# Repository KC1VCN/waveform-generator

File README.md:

# Simple Waveform Generator

## Introduction

The waveform generator is a simple printed circuit board (PCB) designed to generate sinusoidal, triangular, and square waveforms, with usable frequencies up to 10 MHz depending on the waveform type and acceptable output distortion or attenuation. The PCB was designed as an Arduino UNO R3 shield, with the Arduino board acting as the controller. Commands can be sent through the USB port from a computer using a simple Python GUI or hardware API, providing both graphical and programmatic control.

The board also has four external digital inputs with debouncing circuits. These inputs can be connected to rotary encoders to adjust the signal frequency and amplitude. This feature is useful for implementing a standalone audio signal generator in a small enclosure.

The waveform generator PCB supports adjustment of the following output signal parameters:

- Frequency
- Amplitude
- DC offset
- Waveform type (sinusoid, triangle, or square)

The following files are provided as part of this project:

- KiCad v10.0.0 project files for the complete PCB
- Firmware source code for the Arduino UNO R3 and the associated `Makefile`
- Python GUI and hardware API

The following sections provide more details about the circuit design, PCB implementation, software control, and measurement results. The supplied files are intended to help users reproduce the hardware and explore its capabilities.

---

## Printed Circuit Board

Photographs of the waveform generator PCB is shown in Figs. 1a–b. The bare PCB was manufactured through DigiKey's DKRed program using a four-layer stackup (www.digikey.com).

<figure>
  
  <figcaption><b>Figure 1a:</b> Printed circuit board of the waveform generator.</figcaption>
</figure>
<br>
<br>

<figure>
  
  <figcaption><b>Figure 1b:</b> Waveform generator attached to Arduino UNO R3.</figcaption>
</figure>
<br>
<br>

The stackup of the PCB is shown in Fig. 2.

<figure>
  
  <figcaption><b>Figure 2:</b> PCB stackup (DigiKey DKRed four-layer stackup).</figcaption>
</figure>
<br>
<br>

All surface-mount components were selected in 0603 or larger package sizes, and all IC packages were chosen without a central exposed pad and with a lead pitch of at least 0.5 mm. These choices make manual PCB assembly easier if necessary. 

For manual assembly, it is recommended to solder the header pins first while the PCB, header pins, and Arduino board are stacked together. This helps ensure that the header pins align properly with the Arduino board. Then, perform a basic DC test by powering the Arduino board and verifying the +5 V and +3.3 V supply rails on the PCB. You may then proceed with the remaining components. An ESD-dissipative work surface and wrist strap are strongly recommended. A binocular microscope is also useful for manual assembly. Finally, liquid rosin solder flux can significantly help when soldering fine-pitch IC packages by allowing the solder to flow more smoothly.

---

## Connecting the Waveform Generator

To program the Arduino UNO R3 microcontroller or control the waveform generator, connect the Arduino board to your computer using a USB cable. No additional drivers should normally be required on Linux. However, you may need to add your user account to the `dialout` group to access the USB serial port. The waveform generator receives its power from the Arduino board.

Control commands for the waveform generator are sent through the same Arduino UNO R3 USB connector. Therefore, only one application (the GUI, hardware API, or programming tool) should access the serial port at a time.

> [!NOTE]
> When the computer software opens the serial port, the Arduino board may reset as part of the normal bootloader startup sequence. If programming is not initiated, the microcontroller proceeds to the application's `main` function. Allow sufficient time for this startup sequence after opening the serial port, since the microcontroller cannot process commands immediately.

---

## Waveform Generation

The core of the waveform generator PCB is the Analog Devices AD9833 programmable waveform generator IC. With a 25 MHz reference clock, this chip supports output frequencies up to 12.5 MHz and provides a 28-bit frequency tuning word. It has two frequency registers and two phase registers, enabling FSK and PSK modulation. Once these registers are programmed with the desired frequency or phase values, the output can be switched using a register-select command. Sinusoidal, triangular, and square waveforms are supported. Since the signal path following the AD9833 is DC-coupled (with no DC-blocking capacitor), the PCB can also generate signals at very low frequencies.

To suppress unwanted high-frequency spectral components, a fifth-order elliptic reconstruction (anti-imaging) low-pass filter was designed after the AD9833. This provides a relatively clean output spectrum at frequencies up to 10 MHz. Without this filter, spectral images from the sampled waveform would become increasingly close to the desired signal as the output frequency approaches the Nyquist frequency. A relatively sharp cutoff is therefore desirable, motivating the choice of an elliptic filter design.

### Gain Control

The gain control block is based on a multiplying digital-to-analog converter (DAC) architecture. For this purpose, the Analog Devices AD5452 12-bit high-bandwidth multiplying DAC and AD8062 operational amplifier were used. This configuration provides an output voltage swing of one polarity before DC-offset adjustment. Although this approach offers a wide gain adjustment range, the DAC and the associated high-frequency compensation of the op-amp limit the overall bandwidth of the waveform generator.

### DC Offset

Since the AD8062 op-amp in the gain control stage is used in an inverting configuration, its output is negative before offset adjustment. A DC-offset control was therefore implemented to shift the output DC level. This helps to generate output waveforms with symmetric swings. The Analog Devices AD5270 digital potentiometer provides an adjustable voltage to the noninverting input of the AD8062. A series capacitor can also be added at the output to block DC completely if necessary. Note, however, that this would introduce a low-frequency cutoff.

Two points are worth mentioning regarding the AD5270 compared with the AD9833 and AD5452. First, the SPI timing configuration used for the AD5270 is CPOL = 0 and CPHA = 1, whereas the AD9833 and AD5452 are driven using CPOL = 1 and CPHA = 0. This difference must be handled in software because the ICs share the SPI clock line from the Arduino UNO R3. Second, a pull-up resistor is required on the AD5270 SPI data output (SDO) pin, even if readback is not used. Analog Devices Product/Process Change Notice PCN 10_0354 (December 14, 2010) describes a potential malfunction if the pin is left floating.

### Negative Voltage Supply

To generate the negative supply voltage required by the AD8062 op-amp, the Analog Devices MAX1680 switched-capacitor voltage converter was used. Low-ESR ceramic capacitors are important for efficient charge-pump operation and for minimizing switching ripple on the generated supply rail.

---

## Rotary Encoder Inputs

The waveform generator board supports two rotary encoders for adjusting frequency and amplitude when configured as a standalone audio signal generator. One suitable example is the Bourns `PEC09-2315F-N0015` rotary encoder. The connection diagram for the encoders is shown in Fig. 3.

<figure>
  
  <figcaption><b>Figure 3:</b> Connection diagram of the rotary encoders for a standalone waveform generator.</figcaption>
</figure>
<br>
<br>

In standalone operation, the generator remains within the frequency and gain limits preset in the firmware. The default limits are listed below and can be modified in the firmware source code:

| Parameter           | Value       |
|---------------------|-------------|
| Minimum frequency   | 20 Hz       |
| Maximum frequency   | 20,000 Hz   |
| Frequency step      | 100 Hz      |
| Minimum gain        | 0           |
| Maximum gain        | 4095        |
| Gain step           | 100         |

---

## Measurement Results

This section presents basic measurement results for the waveform generator. All measurements were performed using a Siglent SVA-1015X spectrum analyzer at room temperature. Note that these measurements are intended to characterize the performance of the waveform generator under the test conditions used and should not be interpreted as guaranteed specifications over the full range of operating conditions.

Fig. 4 shows the sinusoidal output level versus frequency at different gain settings. For a given gain setting, the output level remains nearly constant up to 2 MHz. Above 2 MHz, the level begins to decrease due to the limited bandwidth of the signal chain.

<figure>
  
  <figcaption><b>Figure 4:</b> Output signal level vs. frequency.</figcaption>
</figure>
<br>
<br>

Fig. 5 shows the sinusoidal output level versus gain setting at different frequencies. The generator provides approximately 50 dB of linear gain-control range up to 100 kHz. Beginning near 1 MHz, this range decreases, reaching approximately 35 dB at 2 MHz.

<figure>
  
  <figcaption><b>Figure 5:</b> Output signal level vs. gain setting.</figcaption>
</figure>
<br>
<br>

The output spectra of sinusoidal signals at different frequencies are shown in Figs. 6a–e. The gain setting for these measurements was 2048 (half scale). 

<figure>
  
  <figcaption><b>Figure 6a:</b> Harmonic levels at 10 kHz (gain: 2048).</figcaption>
</figure>
<br>
<br>

<figure>
  
  <figcaption><b>Figure 6b:</b> Harmonic levels at 100 kHz (gain: 2048).</figcaption>
</figure>
<br>
<br>

<figure>
  
  <figcaption><b>Figure 6c:</b> Harmonic levels at 1 MHz (gain: 2048).</figcaption>
</figure>
<br>
<br>

<figure>
  
  <figcaption><b>Figure 6d:</b> Harmonic levels at 2 MHz (gain: 2048).</figcaption>
</figure>
<br>
<br>

<figure>
  
  <figcaption><b>Figure 6e:</b> Harmonic levels at 10 MHz (gain: 2048).</figcaption>
</figure>
<br>
<br>

---

## FSK and PSK Modulation

The controller also provides a simple way to test the frequency-shift keying (FSK) and phase-shift keying (PSK) capabilities of the AD9833. These features are intended only for demonstration and have not been optimized for performance. You can experiment with them using a spectrum analyzer with demodulation capabilities or a suitable demodulator. The transmitted test message is "Hello World!", but it can be changed in the Python GUI.

At the beginning of each packet, the controller transmits the following synchronization sequence. The receiver should synchronize to this bit pattern for optimal results:

```text
10101010101010100000011100010010
```

Two hardware parameters may need adjustment for reliable operation. The first is the AD9833 reference-clock frequency, which determines the generated carrier frequencies. The PCB uses a nominal 25 MHz oscillator, but the actual frequency may differ slightly. The actual clock frequency can be estimated using a spectrum analyzer or measured directly with a frequency counter. The deviation from the nominal 25 MHz can be specified through the `CLOCK_TRIM` global variable in kHz. The default correction of 8.5 kHz was determined experimentally by matching the generated carrier frequency to the spectrum analyzer reading. Since this adjustment also depends on the accuracy of the spectrum analyzer's frequency reference, it should not be considered an absolute calibration. 

The second parameter is the microcontroller clock frequency, which affects the symbol timing. The Arduino UNO R3 normally operates at 16 MHz. For simplicity, symbol timing is implemented using software-controlled delay loops rather than hardware timer interrupts. These delays are adjusted to obtain a nominal symbol rate of 3 ksps, accounting for the additional execution time introduced by the AD9833 register select commands. Although a hardware timer-based approach would provide more predictable timing, software-controlled delays were considered sufficient for this demonstration. If the received eye diagram drifts, you may need to adjust these delays.

The following figures show FSK and binary PSK (BPSK) test results obtained using the waveform generator PCB.

<figure>
  
  <figcaption><b>Figure 7:</b> FSK modulation test of the waveform generator.</figcaption>
</figure>
<br>
<br>

<figure>
  
  <figcaption><b>Figure 8:</b> BPSK modulation test of the waveform generator.</figcaption>
</figure>
<br>
<br>

---

## Arduino UNO R3 Programming

The Arduino UNO R3 microcontroller can be programmed using the `avr-gcc` C compiler and the `avrdude` programming utility. The versions used during development are listed below:

| Design Tool    | Version                                     |
|----------------|---------------------------------------------|
| avr-gcc        | v7.3.0, AVR-8-bit-GNU-Toolchain-3.7.0-1796  |
| avrdude        | v7.3-20240715                               |

After installing these tools, download the firmware source files from the repository into a suitable directory. Then connect the Arduino UNO R3 board to your computer using a USB cable as described earlier.

> [!NOTE]
> After connecting the UNO R3 board, verify the serial device name assigned by Linux and update the `AVRDUDE_PORT` parameter in the `Makefile` accordingly.
>

> [!NOTE]
> Ensure that the directories containing the `avr-gcc` and `avrdude` executables are included in your `PATH` environment variable so Linux can locate the tools.
>

To compile the firmware, run the following command in the source directory:

```bash
make
```

To program the Arduino UNO R3 microcontroller, run:

```bash
make program
```

To remove previously compiled object files and start with a clean build, run:

```bash
make clean
```

---

## Graphical User Interface

A basic GUI and hardware API are provided to demonstrate the waveform generator's capabilities. Connecting an oscilloscope to the generator output while experimenting with the controls is recommended.

The GUI and hardware API were developed using **Python 3.9** on **Linux**. The reference platform was **RHEL 9.7**, although the software should also run on other Linux distributions if all dependencies are installed. The Python modules and versions used for the GUI and API are listed below. Note that the API itself requires only the `pyserial` module.

| Module      | Version |
|-------------|---------|
| PySide6     | 6.10.1  |
| pyserial    | 3.5     |

<figure>
  
  <figcaption><b>Figure 9:</b> GUI of the waveform generator.</figcaption>
</figure>
<br>
<br>

In the GUI, each register control provides a dial knob and a keyboard entry field. The up/down arrow keys and Page Up/Page Down keys adjust the dial values in normal and larger steps, respectively. The small selector buttons below the frequency display change the tuning multiplier for the frequency dial.

The entry fields allow register values to be entered directly from the keyboard. Signed values are also supported for quickly increasing or decreasing the corresponding register value. For example, entering `+1000` in the frequency field increases the displayed frequency by 1 kHz. Holding down the `Enter` key while the field is active repeatedly increases the frequency in 1 kHz steps. 

---

## Waveform Generator Command Reference

The waveform generator firmware provides a simple, SCPI-inspired command interface for controlling the waveform generator.

### Serial Port Settings

The default serial port settings used by the firmware are shown in the following Python snippet:

```python
port = serial.Serial(p.device)

port.baudrate=57600
port.bytesize=8
port.parity=serial.PARITY_NONE
port.stopbits=serial.STOPBITS_ONE
port.timeout=0.5

port.flushInput()
port.flushOutput()
```

### API Handshake

A simple handshake protocol is implemented between the firmware and the hardware API. Before sending a command to the Arduino, the API must wait until the microcontroller sends the `READY` word. The command can then be sent. After processing the command, the microcontroller returns the `DONE` word.

The following Python snippet can be used to read handshake messages from the microcontroller. Note that this function simply returns the received message without interpreting its contents. If no message is received within approximately one second, it returns False. The calling function must check the returned value (READY, DONE, or False) and respond accordingly.

```python
def wait():
    start_time = time.time()
    timeout_expiry = start_time + 1.0

    while time.time() < timeout_expiry:
        value = port.readline().decode().strip('\n')

        if (value != ''):
            return value
    
    return False
```

### Sending API Commands and Receiving Replies

The API supports two types of commands: those that set a parameter and those that query a parameter. A command can be sent to the microcontroller using the following Python snippet:

```python
port.write(command.encode())
```

For a command that queries a parameter, the microcontroller replies with a value. The returned value can be read using the following Python snippet:

```python
value = port.readline().decode().strip('\n')
```

Note that query commands return values stored in the microcontroller memory. In the current implementation, the microcontroller does not read back the actual chip registers over SPI. These queries therefore help verify that the microcontroller received the intended values from the computer, rather than confirming the chip register contents.

The available hardware API commands are described in the following sections.

### Set Output

```
output:<freq_select>:<phase_select>:\n
```

Selects the active frequency and phase output registers. Each register selection can be either `0` or `1`. 

The synthesizer provides two frequency registers and two phase registers. Once programmed, the active registers can be switched to provide FSK or PSK modulation.

### Set Waveform

```
wave:<type>:\n
```

Selects the output waveform type. The available values are `0` (sinusoid), `1` (triangle), `2` (square, *f*<sub>out</sub>/2), `3` (square, *f*<sub>out</sub>), and `4` (reset).

### Set Frequency

```
freq:<reg>:\n
```

Sets the frequency register value of the active output. The \<reg\> parameter must be between 0 and 268,435,455.

### Set Frequency in Hertz

```
freq-hz:<freq>:\n
```

Sets the frequency of the active output in hertz. The \<freq\> parameter must be between 0 and 10,000,000.

### Get Frequency

```
freq?:\n
```

Returns the frequency register value of the active output from the microcontroller.

### Set Phase

```
phase:<reg>:\n
```

Sets the phase register value of the active output. The \<reg\> parameter must be between 0 and 4095.

### Set Phase in Degrees

```
phase-deg:<phase>:\n
```

Sets the phase of the active output in degrees. The \<phase\> parameter must be between 0 and 360.

### Get Phase

```
phase?:\n
```

Returns the phase register value of the active output from the microcontroller.

### Set Gain

```
gain:<gain>:\n
```

Sets the gain register value. The \<gain\> parameter must be between 0 and 4095.

### Get Gain

```
gain?:\n
```

Returns the gain register value from the microcontroller.

### Set Offset

```
offset:<offset>:\n
```

Sets the DC offset register value. The \<offset\> parameter must be between 0 and 1023.

### Get Offset

```
offset?:\n
```

Returns the DC offset register value from the microcontroller.

---

## License

The hardware design, PCB design files, microcontroller firmware, Python software, and other source material in this repository are licensed under the **CERN Open Hardware Licence Version 2 – Weakly Reciprocal (CERN-OHL-W-2.0)**, unless otherwise noted.

Commercial use is permitted under the terms of CERN-OHL-W-2.0. Modified Covered Source must retain the applicable Notices and include the modification notice required by the license, including the date and a brief description of the modifications. Products made using the Covered Source must provide the Complete Source or identify the Source Location as required by the license.

The full license text is provided in the [`LICENSE`](LICENSE) file, and project-specific attribution and Source Location information are provided in the [`NOTICE`](NOTICE) file.

Third-party software used with this project, including avr-gcc, avrdude, and the required Python modules, is not part of the Covered Source in this repository and remains subject to its respective license.

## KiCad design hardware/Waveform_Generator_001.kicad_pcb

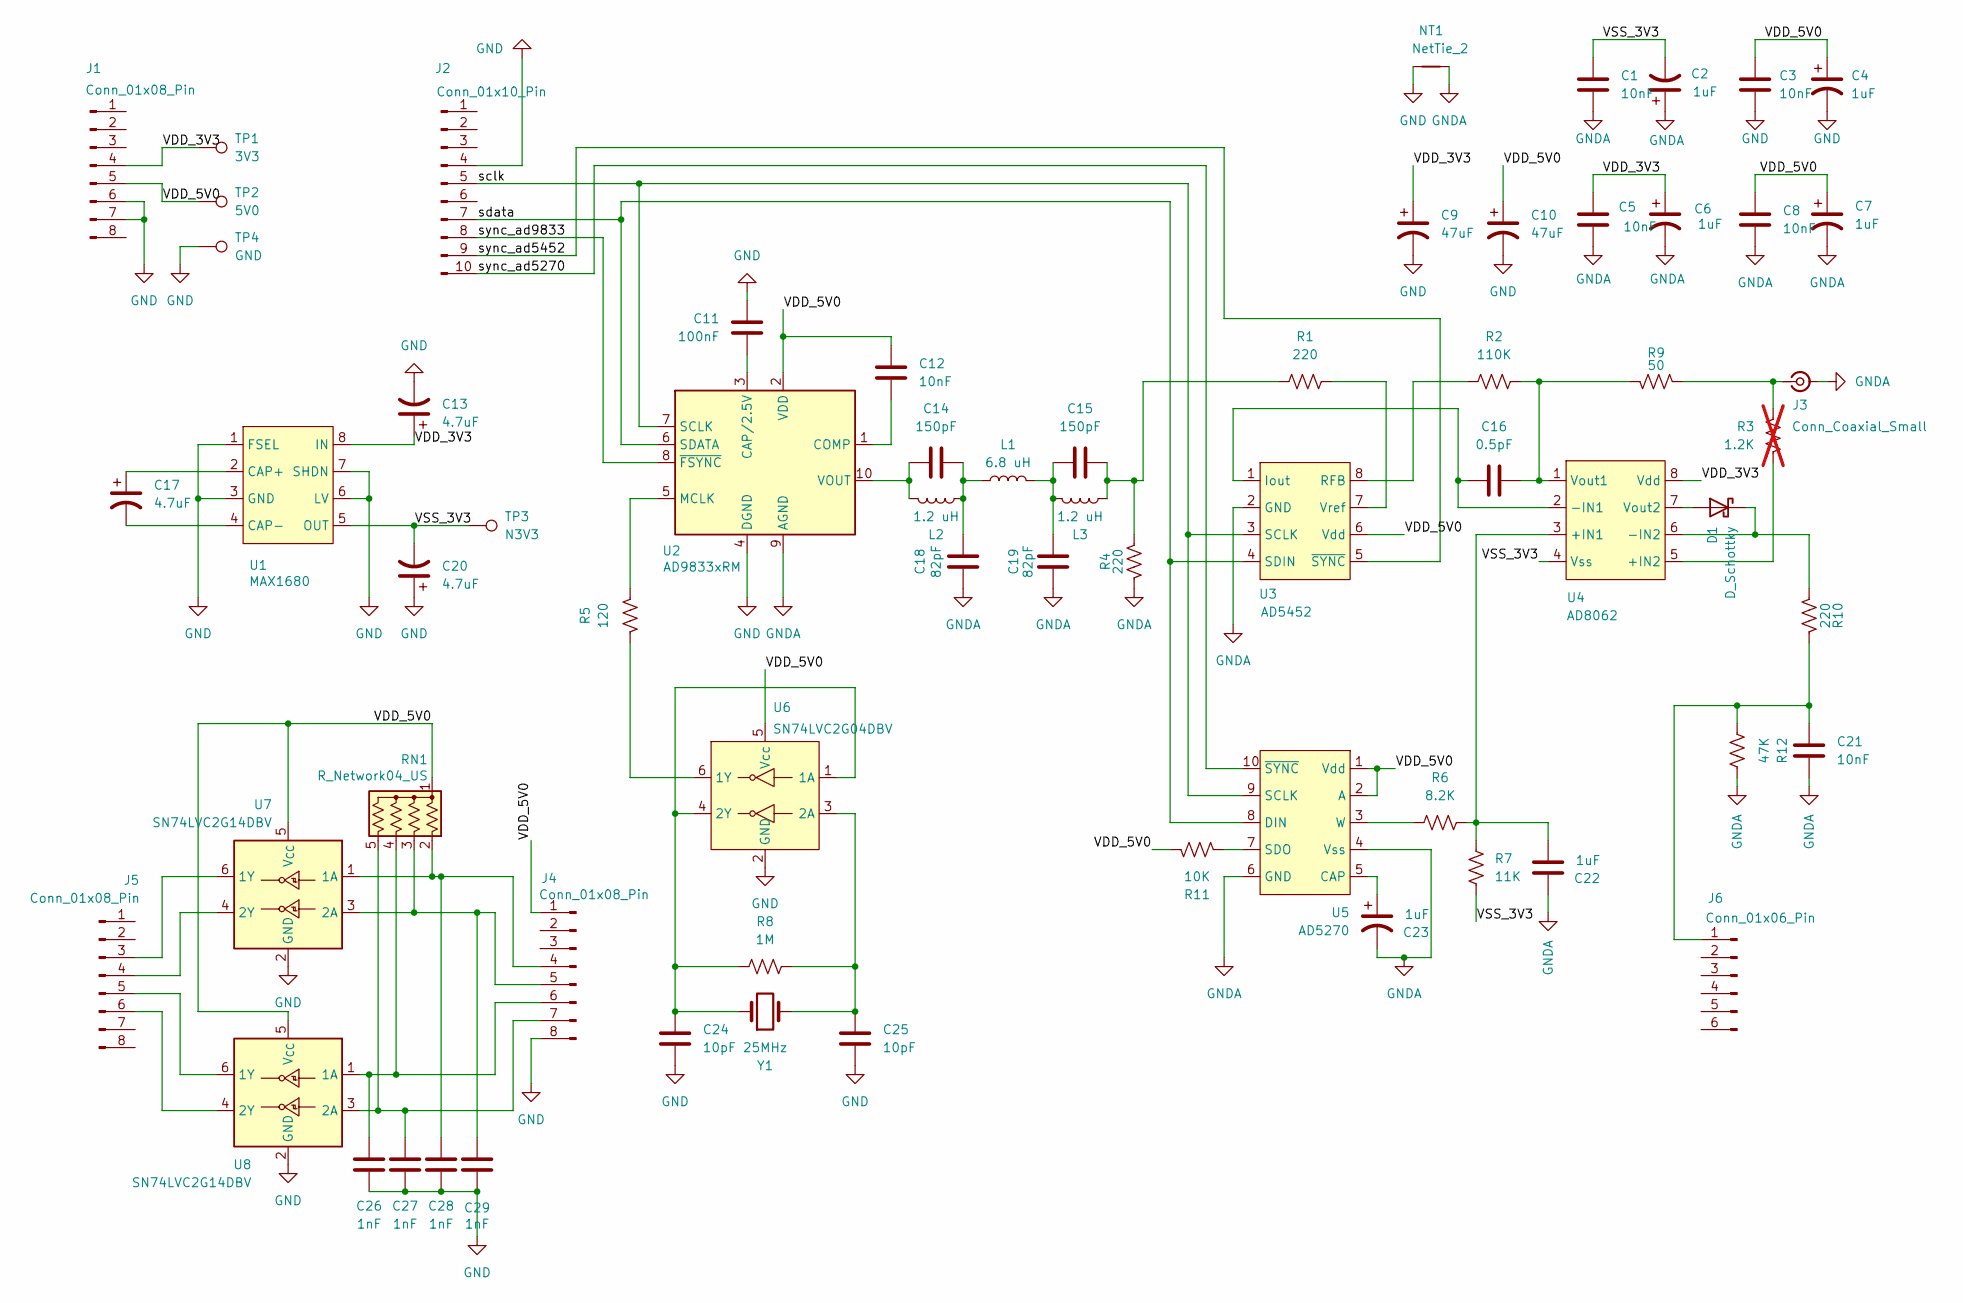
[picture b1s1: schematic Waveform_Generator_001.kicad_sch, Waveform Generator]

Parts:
C1, C3, C5, C8, C12, C21: 10nF; C_0805_2012Metric; Manufacturer Part No KGM21NR71H103JM; DIGIKEY Part No 478-KGM21NR71H103JMCT-ND
C2, C22: 1uF; C_1206_3216Metric; Manufacturer Part No GMK316BJ105MLHT; DIGIKEY Part No 587-6316-1-ND
C4, C6, C7, C23: 1uF; C_1206_3216Metric; Manufacturer Part No T491A105K025AT; DIGIKEY Part No 399-3680-1-ND
C9, C10: 47uF; CP_EIA-6032-15_Kemet-U; Manufacturer Part No T491C476K016AT7280; DIGIKEY Part No 399-T491C476K016AT7280CT-ND
C11: 100nF; C_0805_2012Metric; Manufacturer Part No KGM21NR71H104JT; DIGIKEY Part No 478-KGM21NR71H104JTCT-ND
C13, C17, C20: 4.7uF; C_1206_3216Metric; Manufacturer Part No UMK316ABJ475MLHT; DIGIKEY Part No 587-6377-1-ND
C14, C15: 150pF; C_0603_1608Metric; Manufacturer Part No KGM15ACG2A151FT; DIGIKEY Part No 478-KGM15ACG2A151FTCT-ND
C16: 0.5pF; C_0603_1608Metric; Manufacturer Part No KGM15ACG1H0R5BT; DIGIKEY Part No 478-KGM15ACG1H0R5BTCT-ND
C18, C19: 82pF; C_0603_1608Metric; Manufacturer Part No KGM15ACG2A820FT; DIGIKEY Part No 478-KGM15ACG2A820FTCT-ND
C24, C25: 10pF; C_0603_1608Metric; Manufacturer Part No KGM15ACG1H100JT; DIGIKEY Part No 478-KGM15ACG1H100JTCT-ND
C26, C27, C28, C29: 1nF; C_0603_1608Metric; Manufacturer Part No KGM15ACG1H102JT; DIGIKEY Part No 478-KGM15ACG1H102JTCT-ND
D1: D_Schottky; D_0603_1608Metric; Manufacturer Part No SD0603S040S0R2; DIGIKEY Part No 478-7798-1-ND
J1, J4, J5: Conn_01x08_Pin; PinHeader_1x08_P2.54mm_Vertical; Manufacturer Part No 0022284080; DIGIKEY Part No WM50014-08-ND
J2: Conn_01x10_Pin; PinHeader_1x10_P2.54mm_Vertical; Manufacturer Part No 0022284100; DIGIKEY Part No WM50014-10-ND
J3: Conn_Coaxial_Small; SMA_Amphenol_901-143_Horizontal; Manufacturer Part No 132136; DIGIKEY Part No ACX1232-ND
J6: Conn_01x06_Pin; PinHeader_1x06_P2.54mm_Vertical; Manufacturer Part No 0022284060; DIGIKEY Part No WM50014-06-ND
L1: 6.8 uH; SMD-0806; Manufacturer Part No LSQMB201616T6R8J; DIGIKEY Part No 587-LSQMB201616T6R8JCT-ND
L2, L3: 1.2 uH; SMD-0806; Manufacturer Part No LSQMB201616T1R2J; DIGIKEY Part No 587-LSQMB201616T1R2JCT-ND
NT1: NetTie_2; NetTie-2_SMD_Pad0.5mm
R1, R4: 220; R_0603_1608Metric; Manufacturer Part No ERJ-3EKF2200V; DIGIKEY Part No P220HCT-ND
R2: 110K; R_0603_1608Metric; Manufacturer Part No ERJ-3EKF1103V; DIGIKEY Part No P110KHCT-ND
R3: 1.2K; R_0603_1608Metric; Manufacturer Part No ERJ-3EKF1201V; DIGIKEY Part No P1.20KHCT-ND; not fitted
R5: 120; R_0603_1608Metric; Manufacturer Part No ERJ-3EKF1200V; DIGIKEY Part No P120HCT-ND
R6: 8.2K; R_0603_1608Metric; Manufacturer Part No ERJ-3EKF8201V; DIGIKEY Part No P8.20KHCT-ND
R7: 11K; R_0603_1608Metric; Manufacturer Part No ERJ-3EKF1102V; DIGIKEY Part No P11.0KHCT-ND
R8: 1M; R_0603_1608Metric; Manufacturer Part No ERJ-3EKF1004V; DIGIKEY Part No P1.00MHCT-ND
R9: 50; R_0603_1608Metric; Manufacturer Part No ERJ-3EKF51R0V; DIGIKEY Part No P51.0HCT-ND
R10: 220; R_0603_1608Metric; Manufacturer Part No ERJ-3EKF2201V; DIGIKEY Part No P2.20KHCT-ND
R11: 10K; R_0603_1608Metric; Manufacturer Part No ERJ-3EKF1002V; DIGIKEY Part No P10.0KHCT-ND
R12: 47K; R_0603_1608Metric; Manufacturer Part No ERJ-3EKF4702V; DIGIKEY Part No P47.0KHCT-ND
RN1: R_Network04_US; R_Array_SIP5; Manufacturer Part No CSC05A0110K0GEK; DIGIKEY Part No CSC10KC-ND
TP1: 3V3; TestPoint_Pad_D1.0mm
TP2: 5V0; TestPoint_Pad_D1.0mm
TP3: N3V3; TestPoint_Pad_D1.0mm
TP4: GND; TestPoint_THTPad_D2.0mm_Drill1.0mm; Manufacturer Part No 5001; DIGIKEY Part No 36-5001-ND
U1: MAX1680; SOIC-8_3.9x4.9mm_P1.27mm; Manufacturer Part No MAX1680ESA+; DIGIKEY Part No MAX1680ESA+-ND
U2: AD9833xRM; MSOP-10_3x3mm_P0.5mm; Manufacturer Part No AD9833BRMZ; DIGIKEY Part No 505-AD9833BRMZ-ND
U3: AD5452; MSOP-8_3x3mm_P0.65mm; Manufacturer Part No AD5452YRMZ; DIGIKEY Part No 505-AD5452YRMZ-ND
U4: AD8062; SOIC-8_3.9x4.9mm_P1.27mm; Manufacturer Part No AD8062ARZ-R7; DIGIKEY Part No 505-AD8062ARZ-R7CT-ND
U5: AD5270; MSOP-10_3x3mm_P0.5mm; Manufacturer Part No AD5270BRMZ-20-RL7; DIGIKEY Part No AD5270BRMZ-20-RL7CT-ND
U6: SN74LVC2G04DBV; SOT-23-6; Manufacturer Part No SN74LVC2G04DBVR; DIGIKEY Part No 296-13261-1-ND
U7, U8: SN74LVC2G14DBV; SOT-23-6; Manufacturer Part No SN74LVC2G14DBVR; DIGIKEY Part No 296-13010-1-ND
Y1: 25MHz; Crystal_HC49-U_Vertical; Manufacturer Part No LFXTAL024901BULK; DIGIKEY Part No 1923-1789-ND

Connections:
/VDD_3V3: C5.2, C6.1, C9.1, C13.1, J1.4, TP1.1 (1_1), U1.8 (IN), U4.8 (Vdd)
/VDD_5V0: C3.1, C4.1, C7.1, C8.1, C10.1, C12.1, J1.5, J4.1, R11.2, RN1.1 (common), TP2.1 (1_1), U2.2 (VDD), U3.6 (Vdd), U5.1 (Vdd), U5.2 (A), U6.5 (Vcc), U7.5 (V_{CC}), U8.5 (V_{CC})
/VSS_3V3: C1.1, C2.2, C20.2, R7.1, TP3.1 (1_1), U1.5 (OUT), U4.4 (Vss)
/sclk: J2.5, U2.7 (SCLK), U3.3 (SCLK), U5.9 (SCLK)
/sdata: J2.7, U2.6 (SDATA), U3.4 (SDIN), U5.8 (DIN)
/sync_ad5270: J2.10, U5.10 (~SYNC)
/sync_ad5452: J2.9, U3.5 (~SYNC)
/sync_ad9833: J2.8, U2.8 (~FSYNC)
GND: C3.2, C4.2, C9.2, C10.2, C11.2, C13.2, C20.1, C24.2, C25.2, C26.2, C27.2, C28.2, C29.2, J1.6, J1.7, J2.4, J4.8, NT1.1, TP4.1, U1.1 (FSEL), U1.3 (GND), U1.6 (LV), U1.7 (SHDN), U2.4 (DGND), U6.2 (GND), U7.2 (GND), U8.2 (GND); also elsewhere on the board
GNDA: C1.2, C2.1, C5.1, C6.2, C7.2, C8.2, C18.2, C19.2, C21.2, C22.2, C23.2, J3.2 (Ext), NT1.2, R4.1, R12.1, U2.9 (AGND), U3.2 (GND), U5.4 (Vss), U5.6 (GND)
unnamed: C14.2, C18.1, L1.1, L2.2
unnamed: C15.1, C19.1, L1.2, L3.1
unnamed: C15.2, L3.2, R1.2, R4.2
unnamed: D1.2 (A), U4.7 (Vout2)
unnamed: D1.1 (K), R10.1, U4.6 (-IN2)
unnamed: J3.1 (In), R3.1, R9.2
unnamed: C28.1, J4.4, RN1.2 (R1), U7.1 (1A)
unnamed: C29.1, J4.5, RN1.3 (R2), U7.3 (2A)
unnamed: C26.1, J4.6, RN1.4 (R3), U8.1 (1A)
unnamed: C27.1, J4.7, RN1.5 (R4), U8.3 (2A)
unnamed: J5.3, U7.6 (1Y)
unnamed: J5.4, U7.4 (2Y)
unnamed: J5.5, U8.6 (1Y)
unnamed: J5.6, U8.4 (2Y)
unnamed: C21.1, J6.1 (Pin_1_1), R10.2, R12.2
unnamed: C17.1, U1.2 (CAP+)
unnamed: C17.2, U1.4 (CAP-)
unnamed: C11.1, U2.3 (CAP/2.5V)
unnamed: C12.2, U2.1 (COMP)
unnamed: R5.2, U2.5 (MCLK)
unnamed: C14.1, L2.1, U2.10 (VOUT)
unnamed: C16.1, U3.1 (Iout), U4.2 (-IN1)
unnamed: R2.2, U3.8 (RFB)
unnamed: R1.1, U3.7 (Vref)
unnamed: C22.1, R6.2, R7.2, U4.3 (+IN1)
unnamed: R3.2, U4.5 (+IN2)
unnamed: C16.2, R2.1, R9.1, U4.1 (Vout1)
unnamed: C23.1, U5.5 (CAP)
unnamed: R11.1, U5.7 (SDO)
unnamed: R6.1, U5.3 (W)
unnamed: C24.1, R8.1, U6.1 (1A), U6.4 (2Y), Y1.1
unnamed: R5.1, U6.6 (1Y)
unnamed: C25.1, R8.2, U6.3 (2A), Y1.2

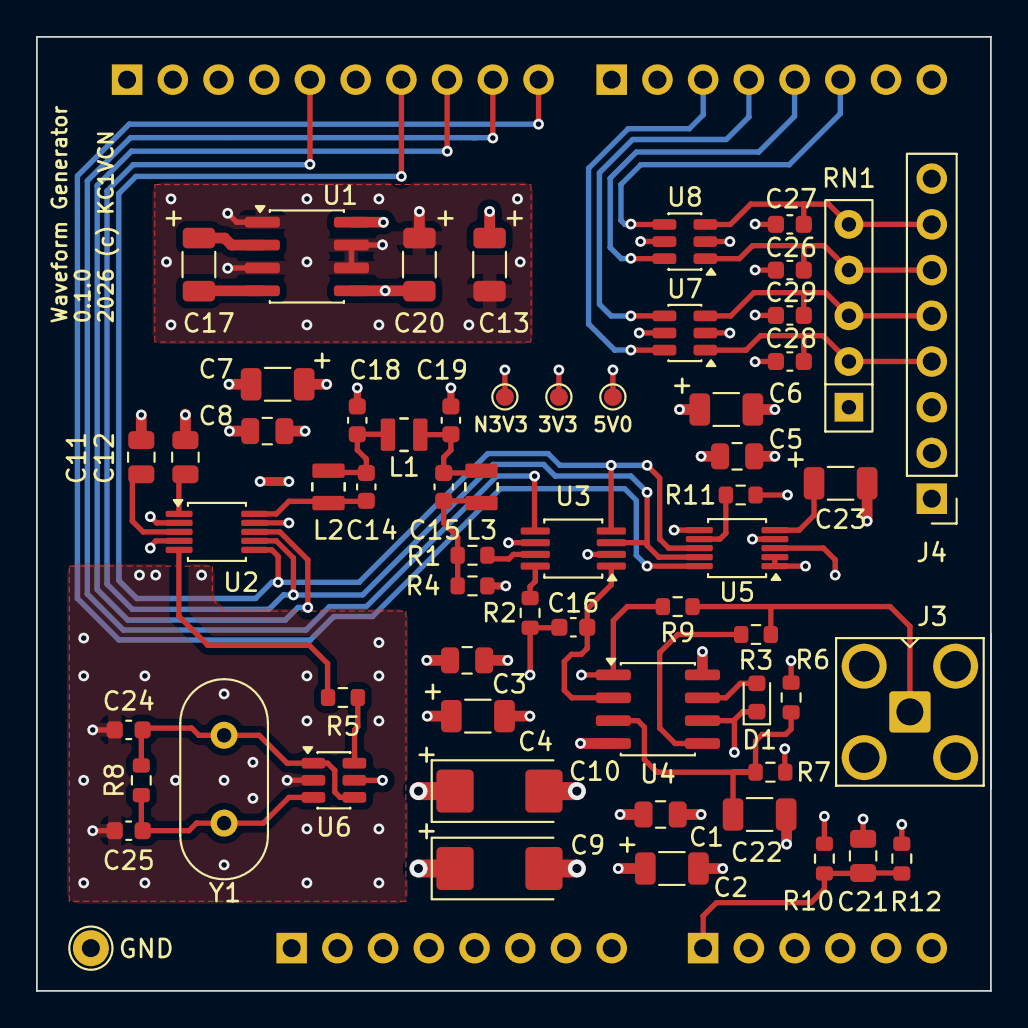
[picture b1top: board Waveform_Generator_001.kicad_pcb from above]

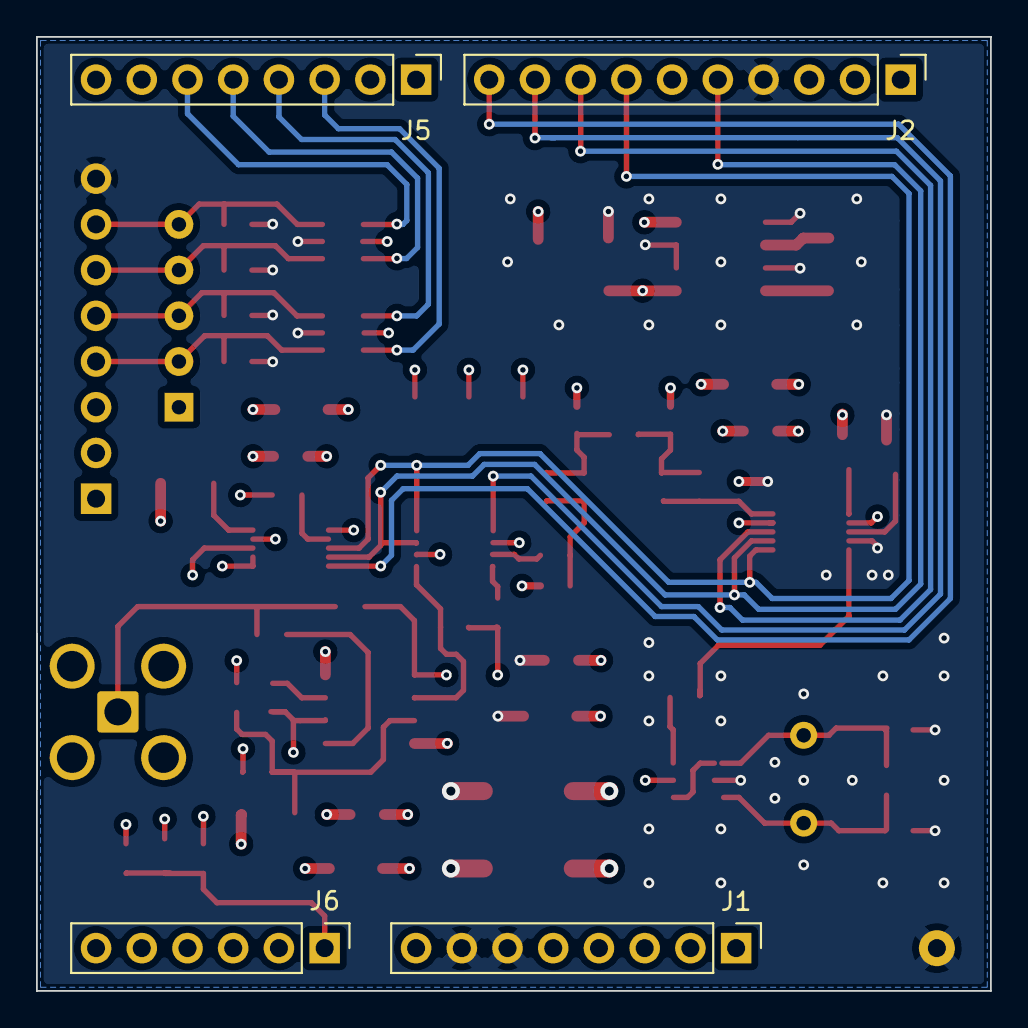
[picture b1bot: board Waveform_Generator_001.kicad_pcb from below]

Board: 4 copper layers, 53.0 x 53.0 mm, 66 parts (4 on the bottom side), 43 nets.

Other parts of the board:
GND: GND; TestPoint_THTPad_D2.0mm_Drill1.0mm

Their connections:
GND: GND.1 (1_1); also elsewhere on the board

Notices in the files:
hardware/Waveform_Generator_001.kicad_sch:
(c) 2026 KC1VCN
